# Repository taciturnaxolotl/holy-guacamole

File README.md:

# Holy Guacamole 🥑

This is a meltybrain style combat robot whose main weapon is simply its own spinning kinetic energy. The BOM is on a google sheet [here](https://docs.google.com/spreadsheets/d/1paAJ0Wakvn5M726pM15FUGLVGKdC47_Wt41PN1yA9PQ/edit?gid=0#gid=0) and the CAD is done in onshape and available [here](https://cad.onshape.com/documents/a046eeb92ff2319e557090a2/w/6774deed54414bae93c63cc1/e/4d0675cbf797ff5c6c8f60bb?renderMode=0&uiState=6a4b13893c4a31ee1cf2e4f3)

The canonical repo for this is hosted on tangled over at [`dunkirk.sh/holy-guacamole`](https://tangled.org/dunkirk.sh/holy-guacamole)

## Repo map

- [`docs/spec.md`](docs/spec.md): the robot and the rev 2 carrier board (4 layers, 2 oz outer copper, 3S only, made by PCBWay)
- [`docs/firmware.md`](docs/firmware.md): what the firmware and the simulator do today
- [`hardware/procurement/bom_rev2.csv`](hardware/procurement/bom_rev2.csv): the rev 2 parts list
- [`cad/rev2/README.md`](cad/rev2/README.md): what the board takes from the chassis (outline, keepouts, placement)
- [`hardware/`](hardware): the KiCad project. Scripts place and route the board, so it can be rebuilt from the schematic:

```sh
cd hardware && kicad-cli sch export netlist -o /tmp/rev2.net guac.kicad_sch
# the next two need KiCad's own python (it ships pcbnew); this is the macOS path
KIPY=/Applications/KiCad/KiCad.app/Contents/Frameworks/Python.framework/Versions/Current/bin/python3
$KIPY scripts/layout_rev2.py && $KIPY scripts/power_rev2.py
sh scripts/route_best_rev2.sh guac.kicad_pcb   # autoroute (Freerouting 2.5, JDK 25+), then stitching and silk
sh scripts/export_pcbway.sh                    # order files into production/pcbway/
```

| | | | |
|---|---|---|---|
|  |  |  |  |

| | |
|---|---|
|  |  |
|  |  |

<p align="center">
    <i><code>&copy; 2026-present <a href="https://dunkirk.sh">Kieran Klukas</a></code></i>
</p>

<p align="center">

</p>

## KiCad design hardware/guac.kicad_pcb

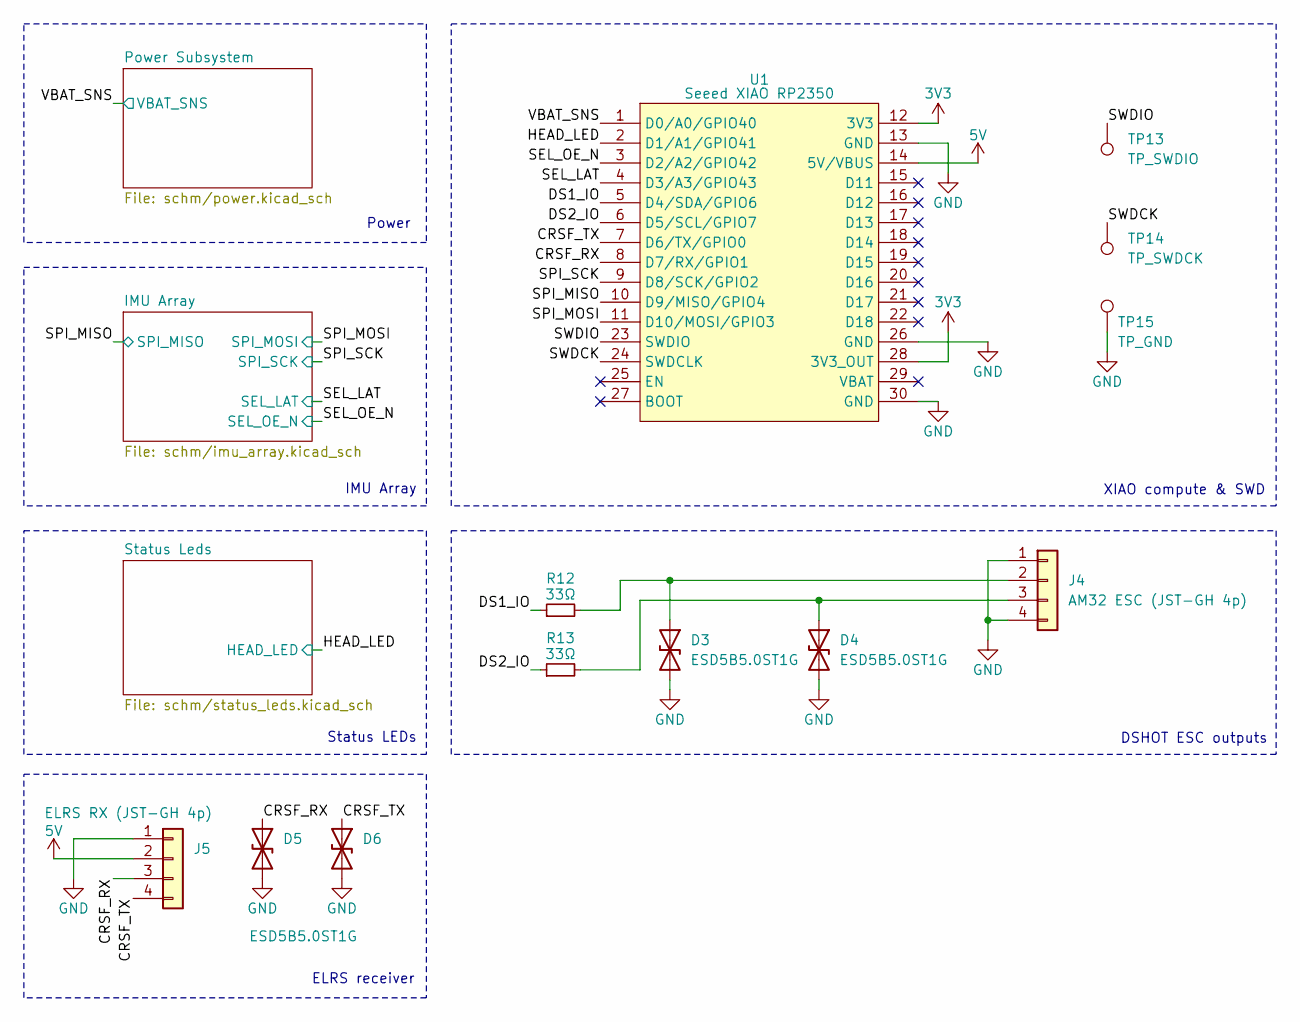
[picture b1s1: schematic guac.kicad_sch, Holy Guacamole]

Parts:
D3, D4, D5, D6: ESD5B5.0ST1G; D_SOD-523
J4: AM32 ESC (JST-GH 4p); JST_GH_SM04B-GHS-TB_1x04-1MP_P1.25mm_Horizontal; LCSC Part NONE
J5: ELRS RX (JST-GH 4p); JST_GH_SM04B-GHS-TB_1x04-1MP_P1.25mm_Horizontal; LCSC Part NONE
R12, R13: 33Ω; R_0402_1005Metric; LCSC Part C3008986
TP13: TP_SWDIO; TestPoint_Pad_D1.0mm; LCSC Part NONE
TP14: TP_SWDCK; TestPoint_Pad_D1.0mm; LCSC Part NONE
TP15: TP_GND; TestPoint_Pad_D1.0mm; LCSC Part NONE
U1: Seeed XIAO RP2350; XIAO-RP2350-SMD; LCSC Part NONE

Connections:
3V3: U1.12 (3V3), U1.28 (3V3_OUT); also elsewhere on the board
5V: J5.2, U1.14 (5V/VBUS); also elsewhere on the board
/CRSF_RX: D5.1 (A1), J5.3, U1.8 (D7/RX/GPIO1)
/CRSF_TX: D6.1 (A1), J5.4, U1.7 (D6/TX/GPIO0)
/DS1_IO: R12.1, U1.5 (D4/SDA/GPIO6)
/DS2_IO: R13.1, U1.6 (D5/SCL/GPIO7)
/HEAD_LED: U1.2 (D1/A1/GPIO41); also elsewhere on the board
/SEL_LAT: U1.4 (D3/A3/GPIO43); also elsewhere on the board
/SEL_OE_N: U1.3 (D2/A2/GPIO42); also elsewhere on the board
/SPI_MISO: U1.10 (D9/MISO/GPIO4); also elsewhere on the board
/SPI_MOSI: U1.11 (D10/MOSI/GPIO3); also elsewhere on the board
/SPI_SCK: U1.9 (D8/SCK/GPIO2); also elsewhere on the board
/SWDCK: TP14.1, U1.24 (SWDCLK)
/SWDIO: TP13.1, U1.23 (SWDIO)
/VBAT_SNS: U1.1 (D0/A0/GPIO40); also elsewhere on the board
GND: D3.2 (A2), D4.2 (A2), D5.2 (A2), D6.2 (A2), J4.1, J4.4, J4.MP, J5.1, J5.MP, TP15.1, U1.13 (GND), U1.26 (GND), U1.30 (GND); also elsewhere on the board
unnamed: D3.1 (A1), J4.2, R12.2
unnamed: D4.1 (A1), J4.3, R13.2

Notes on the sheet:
ELRS receiver
Status LEDs
IMU Array
DSHOT ESC outputs
XIAO compute & SWD
Power

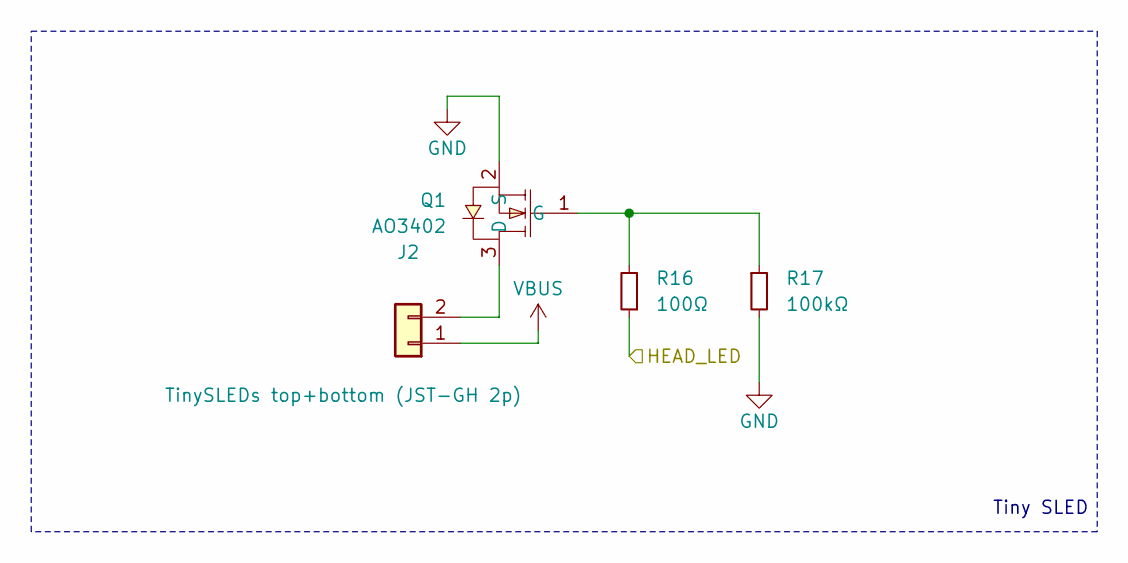
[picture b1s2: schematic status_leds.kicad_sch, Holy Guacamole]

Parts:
J2: TinySLEDs top+bottom (JST-GH 2p); JST_GH_SM02B-GHS-TB_1x02-1MP_P1.25mm_Horizontal; LCSC Part NONE
Q1: AO3402; SOT-23_L2.9-W1.3-P1.90-LS2.4-BR; LCSC Part C14385
R16: 100Ω; R_0402_1005Metric; LCSC Part C1884631
R17: 100kΩ; R_0402_1005Metric; LCSC Part C2077080

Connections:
/HEAD_LED: R16.1; also elsewhere on the board
GND: J2.MP, Q1.2 (S), R17.2; also elsewhere on the board
unnamed: J2.2, Q1.3 (D)
unnamed: Q1.1 (G), R16.2, R17.1
VBUS: J2.1; also elsewhere on the board

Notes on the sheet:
Tiny SLED

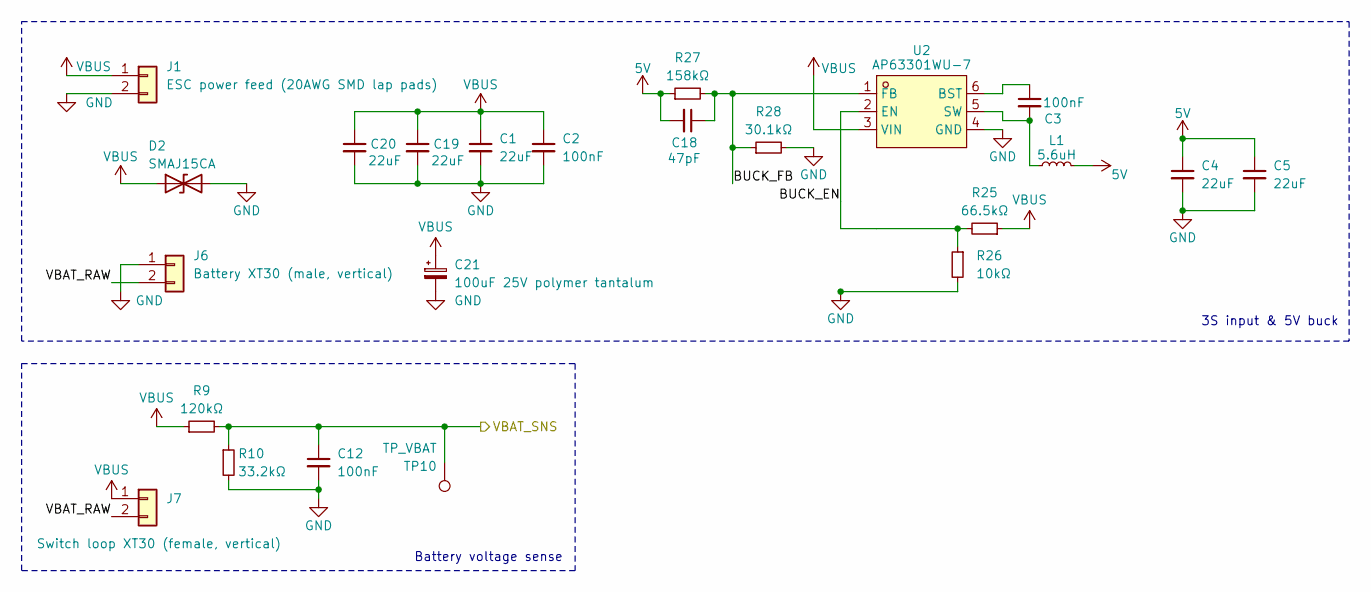
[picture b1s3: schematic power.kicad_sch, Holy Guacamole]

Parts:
C1, C4, C5: 22uF; C_0805_2012Metric; LCSC Part C602037
C2, C3, C12: 100nF; C_0402_1005Metric; LCSC Part C169834
C18: 47pF; C_0402_1005Metric
C19, C20: 22uF; C_0805_2012Metric
C21: 100uF 25V polymer tantalum; CP_EIA-7343-43_Kemet-X
D2: SMAJ15CA; D_SMA; LCSC Part C110044
J1: ESC power feed (20AWG SMD lap pads); SolderLap_20AWG_1x02_2.6x4.0mm_P3.2mm; LCSC Part NONE
J6: Battery XT30 (male, vertical); AMASS_XT30UPB-M_1x02_P5.0mm_Vertical
J7: Switch loop XT30 (female, vertical); AMASS_XT30UPB-F_1x02_P5.0mm_Vertical
L1: 5.6uH; L_Bourns_SRP6060FA; LCSC Part Bourns SRP6060FA-5R6M
R9: 120kΩ; R_0402_1005Metric; LCSC Part C409883
R10: 33.2kΩ; R_0402_1005Metric; LCSC Part C3008937
R25: 66.5kΩ; R_0402_1005Metric; LCSC Part C237746
R26: 10kΩ; R_0402_1005Metric; LCSC Part C844715
R27: 158kΩ; R_0402_1005Metric
R28: 30.1kΩ; R_0402_1005Metric
TP10: TP_VBAT; TestPoint_Pad_D1.0mm; LCSC Part NONE
U2: AP63301WU-7; TSOT-23-6_L2.9-W1.6-P0.95-LS2.8-BL; LCSC Part AP63301WU-7

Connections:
5V: C4.1, C5.1, C18.2, L1.2, R27.1; also elsewhere on the board
/Power Subsystem/BUCK_EN: R25.2, R26.1, U2.2 (EN)
/Power Subsystem/BUCK_FB: C18.1, R27.2, R28.1, U2.1 (FB)
/Power Subsystem/VBAT_RAW: J6.2, J7.2
/VBAT_SNS: C12.1, R9.2, R10.1, TP10.1; also elsewhere on the board
GND: C1.2, C2.2, C4.2, C5.2, C12.2, C19.2, C20.2, C21.2, D2.2 (A2), J1.2, J6.1, R10.2, R26.2, R28.2, U2.4 (GND); also elsewhere on the board
unnamed: C3.1, U2.6 (BST)
unnamed: C3.2, L1.1, U2.5 (SW)
VBUS: C1.1, C2.1, C19.1, C20.1, C21.1, D2.1 (A1), J1.1, J7.1, R9.1, R25.1, U2.3 (VIN); also elsewhere on the board

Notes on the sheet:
Battery voltage sense
3S input & 5V buck

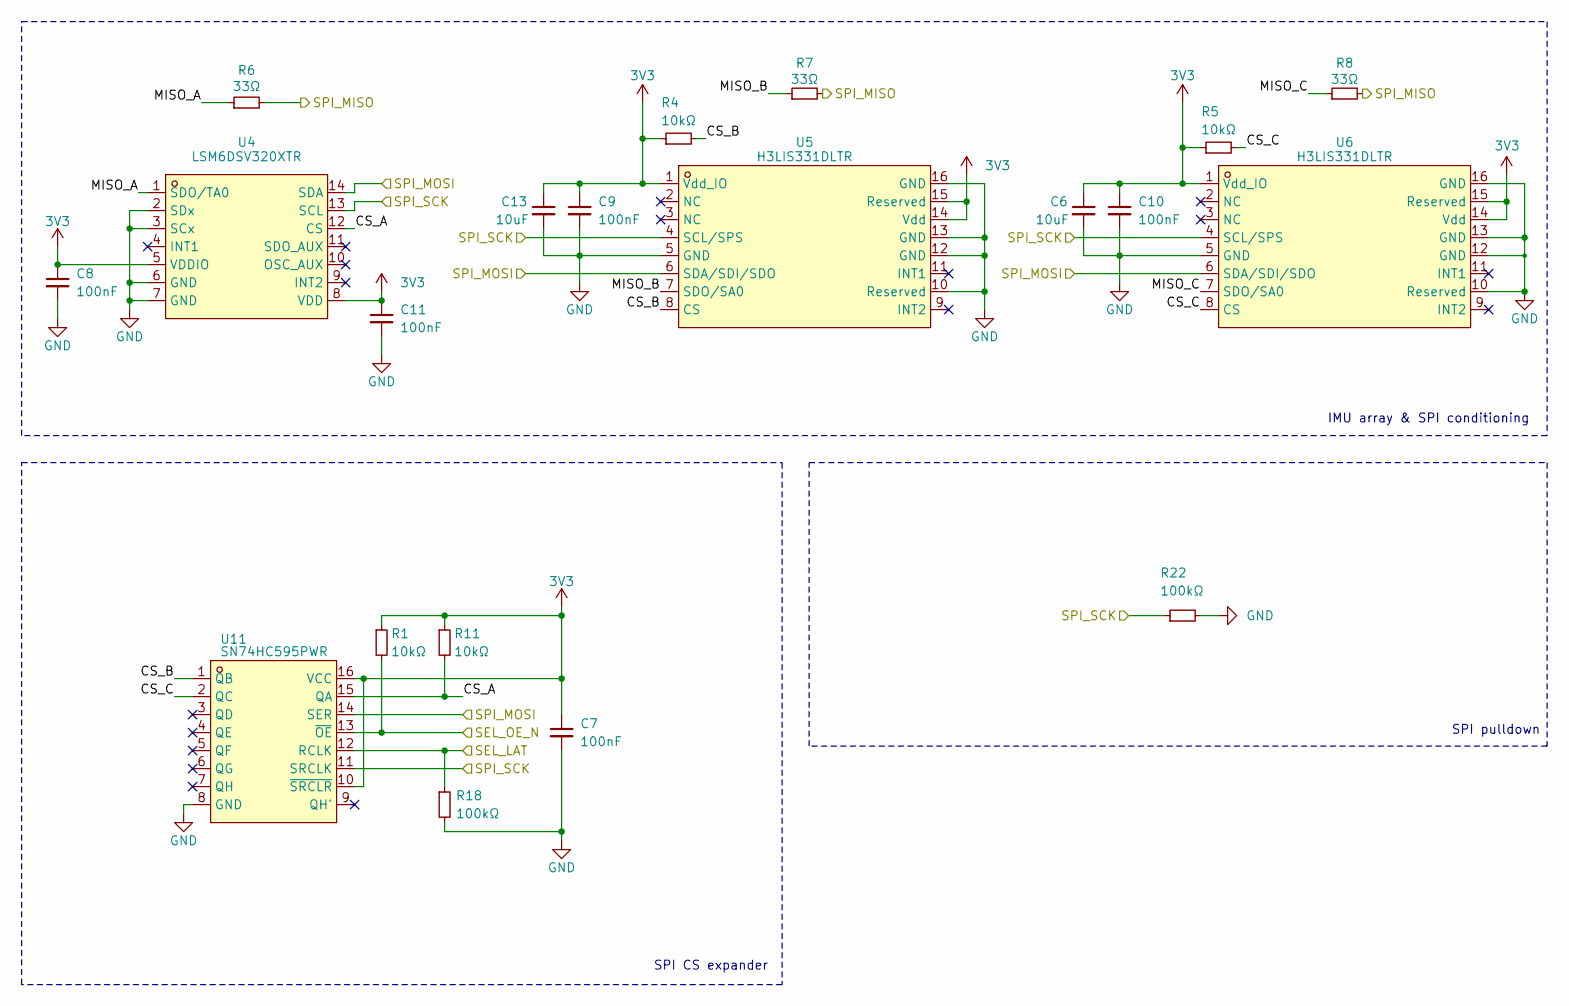
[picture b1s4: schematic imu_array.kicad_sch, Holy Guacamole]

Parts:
C6, C13: 10uF; C_0603_1608Metric; LCSC Part C913532
C7, C8, C9, C10, C11: 100nF; C_0402_1005Metric; LCSC Part C169834
R1, R4, R5, R11: 10kΩ; R_0402_1005Metric; LCSC Part C844715
R6, R7, R8: 33Ω; R_0402_1005Metric; LCSC Part C3008986
R18, R22: 100kΩ; R_0402_1005Metric; LCSC Part C2077080
U4: LSM6DSV320XTR; LGA-14_L3.0-W2.5-P0.50-TL; LCSC Part C26633007
U5, U6: H3LIS331DLTR; LGA-16_L3.0-W3.0-P0.50-BL; LCSC Part C2655074
U11: SN74HC595PWR; TSSOP-16_L5.0-W4.4-P0.65-LS6.4-BL; LCSC Part C273642

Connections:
3V3: C6.1, C7.1, C8.1, C9.1, C10.1, C11.1, C13.1, R1.1, R4.1, R5.1, R11.1, U4.5 (VDDIO), U4.8 (VDD), U5.1 (Vdd_IO), U5.14 (Vdd), U5.15 (Reserved), U6.1 (Vdd_IO), U6.14 (Vdd), U6.15 (Reserved), U11.10 (~SRCLR), U11.16 (VCC); also elsewhere on the board
/IMU Array/CS_A: R11.2, U4.12 (CS), U11.15 (QA)
/IMU Array/CS_B: R4.2, U5.8 (CS), U11.1 (QB)
/IMU Array/CS_C: R5.2, U6.8 (CS), U11.2 (QC)
/IMU Array/MISO_A: R6.1, U4.1 (SDO/TA0)
/IMU Array/MISO_B: R7.1, U5.7 (SDO/SA0)
/IMU Array/MISO_C: R8.1, U6.7 (SDO/SA0)
/SEL_LAT: R18.1, U11.12 (RCLK); also elsewhere on the board
/SEL_OE_N: R1.2, U11.13 (~OE); also elsewhere on the board
/SPI_MISO: R6.2, R7.2, R8.2; also elsewhere on the board
/SPI_MOSI: U4.14 (SDA), U5.6 (SDA/SDI/SDO), U6.6 (SDA/SDI/SDO), U11.14 (SER); also elsewhere on the board
/SPI_SCK: R22.1, U4.13 (SCL), U5.4 (SCL/SPS), U6.4 (SCL/SPS), U11.11 (SRCLK); also elsewhere on the board
GND: C6.2, C7.2, C8.2, C9.2, C10.2, C11.2, C13.2, R18.2, R22.2, U4.2 (SDx), U4.3 (SCx), U4.6 (GND), U4.7 (GND), U5.5 (GND), U5.10 (Reserved), U5.12 (GND), U5.13 (GND), U5.16 (GND), U6.5 (GND), U6.10 (Reserved), U6.12 (GND), U6.13 (GND), U6.16 (GND), U11.8 (GND); also elsewhere on the board

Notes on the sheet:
SPI pulldown
SPI CS expander
IMU array & SPI conditioning

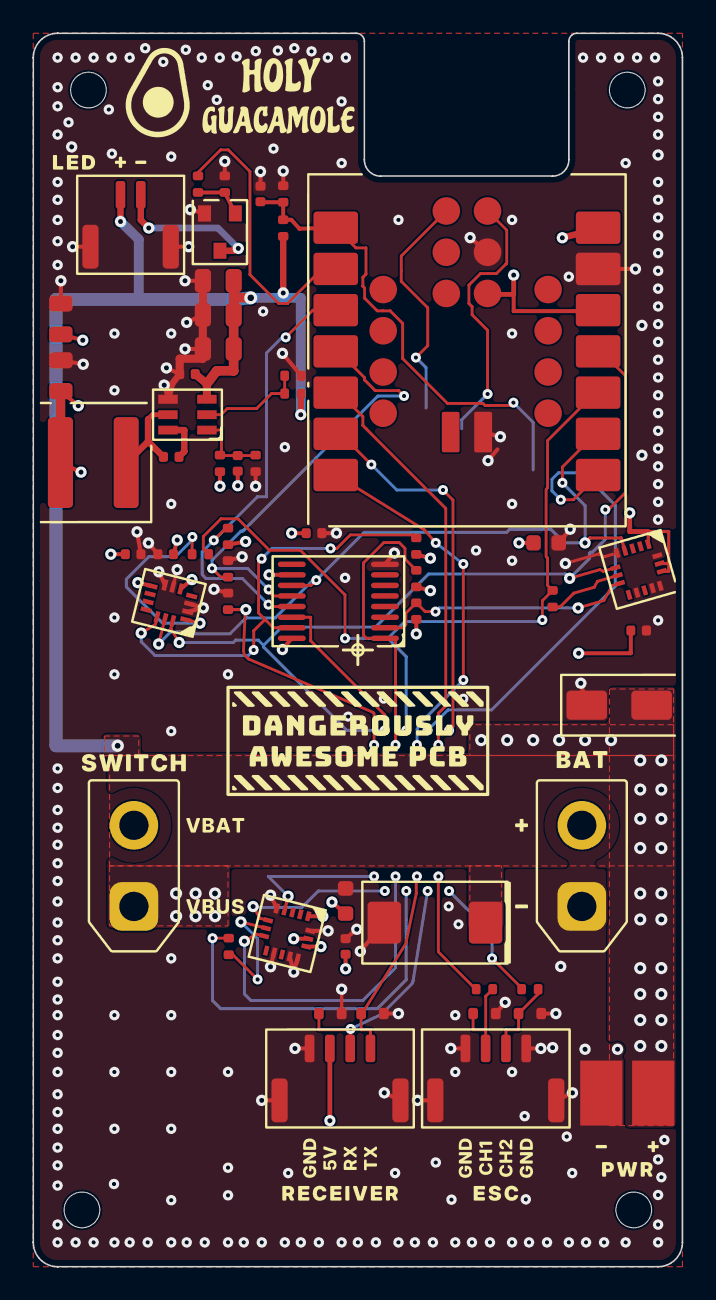
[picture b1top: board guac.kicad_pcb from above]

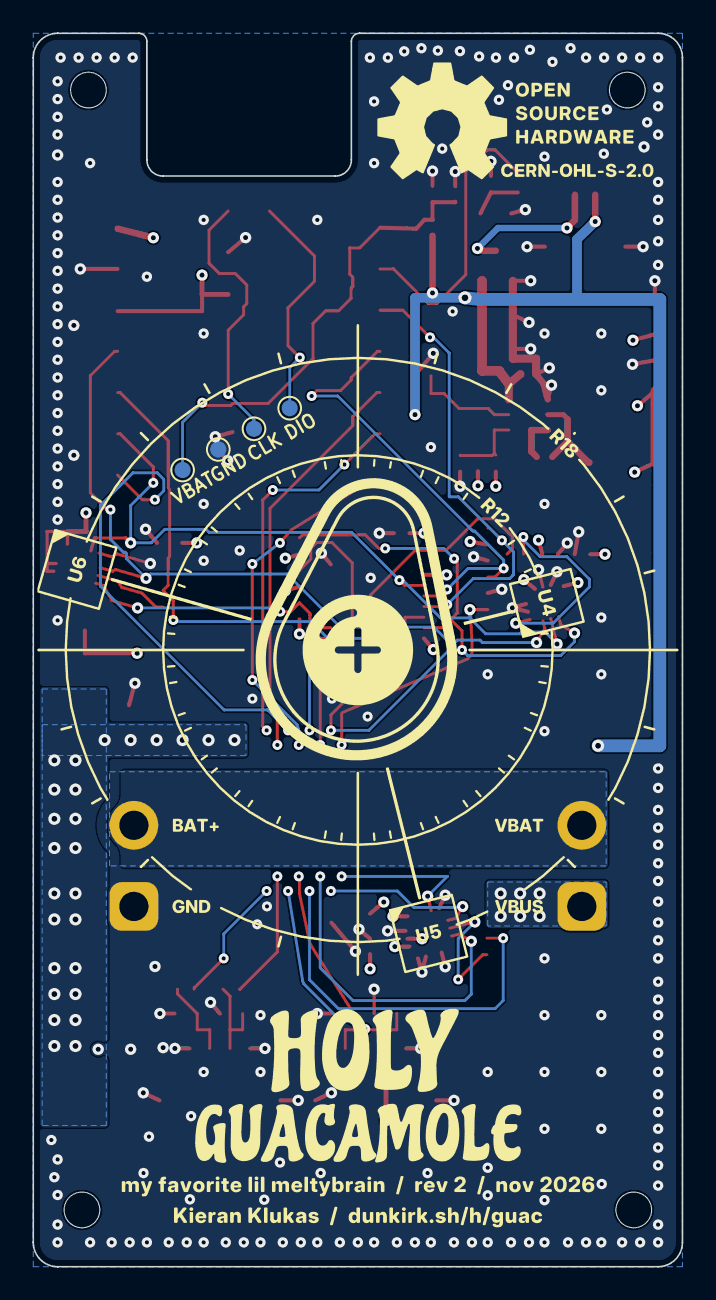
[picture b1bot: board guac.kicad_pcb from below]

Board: 4 copper layers, 40.0 x 76.0 mm, 63 parts (4 on the bottom side), 32 nets.

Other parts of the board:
H1, H2, H3, H4: M2 to ledge heat-set; MountingHole_2.2mm_M2

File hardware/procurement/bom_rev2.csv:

Designators,Qty per board,Manufacturer,Manufacturer Part Number,Description,Supplier,Supplier Part Number
C1 C4 C5 C19 C20,5,TDK,C2012X5R1E226M125AC,22uF 25V X5R 0805 ceramic capacitor,DigiKey,445-9112-1-ND
C2 C3 C7 C8 C9 C10 C11 C12,8,KEMET,C0402C104K3RACTU,100nF 25V X7R 0402 ceramic capacitor,DigiKey,399-14148-1-ND
C6 C13,2,Murata Electronics,GRM185R60J106ME15D,10uF 6.3V X5R 0603 ceramic capacitor,DigiKey,490-10467-1-ND
C18,1,TDK,C1005C0G1H470G050BA,47pF C0G 50V 2% 0402 AP63301 feed-forward capacitor,DigiKey,445-5364-1-ND
C21,1,TBD,TBD,"100uF 25V polymer tantalum, EIA 7343-43, max 4.3 mm tall",,
D2,1,Bourns,SMAJ15CA,15V bidirectional 400W TVS DO-214AC SMA,DigiKey,SMAJ15CABCT-ND
D3 D4 D5 D6,4,onsemi,ESD5B5.0ST1G,Bidirectional 5V ESD diode SOD-523,DigiKey,ESD5B5.0ST1GOSCT-ND
J2,1,JST,SM02B-GHS-TB(LF)(SN),JST-GH 2-pin SMD right-angle header,,
J4 J5,2,JST,SM04B-GHS-TB(LF)(SN),JST-GH 4-pin SMD right-angle header,,
J6,1,AMASS,XT30UPB-M,"XT30 male vertical PCB connector, through-hole",,
J7,1,AMASS,XT30UPB-F,"XT30 female vertical PCB connector, through-hole",,
L1,1,Bourns,SRP6060FA-5R6M,5.6uH shielded power inductor 6.4x6.6mm,DigiKey,SRP6060FA-5R6MCT-ND
Q1,1,Alpha & Omega Semiconductor,AO3402,30V N-channel MOSFET SOT-23,DigiKey,785-1002-1-ND
R1 R4 R5 R11 R26,5,Vishay Dale,CRCW040210K0FKEDHP,10k ohm 1% 0402 resistor,DigiKey,541-10.0KYCT-ND
R6 R7 R8 R12 R13,5,Vishay Dale,CRCW040233R0JNEDC,33 ohm 5% 0402 resistor,DigiKey,541-4009-1-ND
R9,1,Panasonic Industry,ERJ-2RKF1203X,120k ohm 1% 0402 resistor,DigiKey,P120KLCT-ND
R10,1,Vishay Dale,CRCW040233K2FKEDC,33.2k ohm 1% 0402 resistor,DigiKey,541-4092-1-ND
R16,1,Vishay,MCS04020C1000FE000,100 ohm 1% 0402 resistor,DigiKey,MCS0402-100-CFCT-ND
R17 R18 R22,3,Bourns,CR0402-FX-1003GLF,100k ohm 1% 0402 resistor,DigiKey,CR0402-FX-1003GLFCT-ND
R25,1,Vishay Dale,CRCW040266K5FKED,66.5k ohm 1% 0402 resistor (UVLO set; look up the DigiKey number when ordering),DigiKey,
R27,1,Vishay Dale,CRCW0402158KFKTD,158k ohm 1% 0402 AP63301 feedback resistor,DigiKey,541-CRCW0402158KFKTDCT-ND
R28,1,Vishay Dale,CRCW040230K1FKED,30.1k ohm 1% 0402 AP63301 feedback resistor,DigiKey,541-4109-1-ND
U1,1,Seeed Technology,102010550,XIAO RP2350 module; headers supplied loose and not installed,DigiKey,1597-102010550-ND
U2,1,Diodes Incorporated,AP63301WU-7,3.8-32V 3A adjustable forced-PWM synchronous buck TSOT26,Mouser,621-AP63301WU-7
U4,1,STMicroelectronics,LSM6DSV320XTR,6-axis plus high-g IMU LGA-14 2.5x3mm,Mouser,511-LSM6DSV320XTR
U5 U6,2,STMicroelectronics,H3LIS331DLTR,High-g accelerometer LGA-16 3x3mm,DigiKey,497-13903-1-ND
U11,1,Texas Instruments,SN74HC595PWR,8-bit shift register TSSOP-16,DigiKey,296-23258-1-ND

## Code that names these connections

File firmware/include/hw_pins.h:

#pragma once

/*
 * Holy Guacamole carrier PCB (rev 2) pin assignments.
 * Matches the pin table in docs/spec.md. GPIO numbers are for the
 * Seeed XIAO RP2350 (RP2350A); see the SDK's boards/seeed_xiao_rp2350.h.
 */

/* SPI bus (shared: IMUs + SN74HC595 latch) */
#define PIN_SPI_SCK   2   /* XIAO D8/GPIO2 */
#define PIN_SPI_MOSI  3   /* XIAO D10/GPIO3 */
#define PIN_SPI_MISO  4   /* XIAO D9/GPIO4 */
#define SPI_INST      spi0

/* SN74HC595 latch control */
#define PIN_SEL_OE_N  28  /* XIAO D2/A2/GPIO28, active-low output enable */
#define PIN_SEL_LAT   5   /* XIAO D3/GPIO5, latch clock */

/* Latch bit assignments (active-low outputs); QD-QH are NC */
#define LATCH_BIT_CS_A     0  /* QA / pin 15 -> CS_A */
#define LATCH_BIT_CS_B     1  /* QB / pin 1  -> CS_B */
#define LATCH_BIT_CS_C     2  /* QC / pin 2  -> CS_C */

/* Safe latch image: all outputs inactive (high) */
#define LATCH_SAFE  0xFF

/* DSHOT bidirectional (direct RP2350 GPIO, not through latch) */
#define PIN_DSHOT1    6   /* XIAO D4/SDA/GPIO6 -> AM32 ch1 */
#define PIN_DSHOT2    7   /* XIAO D5/SCL/GPIO7 -> AM32 ch2 */

/* CRSF UART to ELRS receiver */
#define PIN_CRSF_TX   0   /* XIAO D6/TX/GPIO0 */
#define PIN_CRSF_RX   1   /* XIAO D7/RX/GPIO1 */
#define CRSF_UART     uart0
#define CRSF_BAUD     420000

/* Battery voltage sense */
#define PIN_VBAT_ADC  26  /* XIAO D0/A0/GPIO26 */
#define ADC_VBAT_CHAN 0   /* ADC channel for GPIO26 */

/* TinySLED heading/status LEDs: AO3402 Q1 gate, high = lit */
#define PIN_HEAD_LED  27  /* XIAO D1/A1/GPIO27 */

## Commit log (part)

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2026-06-26 Add project templates
2026-06-26 feat: git init
2026-06-29 feat: almost full schematic
2026-06-29 feat: organize into hierarchical sheets
2026-06-29 feat: organize subsheets
2026-06-30 feat: organize into better sheets

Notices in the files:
README.md:
https://img.shields.io/static/v1.svg?style=for-the-badge&label=Hardware&message=CERN-OHL-S+v2&logoColor=d9e0ee&colorA=363a4f&colorB=b7bdf8
hardware/guac.kicad_pcb:
SPDX-License-Identifier: CERN-OHL-S-2.0
